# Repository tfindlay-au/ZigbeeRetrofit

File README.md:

# Zigbee Retrofit

### Purpose
This project provide a PCB that will retrofit into an M5Stack Zigbee Unit but replaces the CC2630 with the more common and better supported CC2531 chipset.

Designed in KiCad 6.0.9
The output board measures 50mm x 20mm and contains cutouts for mounting in the case /w lego fittings

The design incorporates a Tag-Connect 10 pad pogo pin (TC-2050-NL) footprint to write/flash firmware.
The design also incorporates a 4-pin Grove connector with UART interface for easy connection with M5Stack Atom products.

The design also uses the following symbols:
- 110990037: Seed Studio Grove connector
- CC2531F256RHAT: TI Chip Zigbee chip
- TC2050-IDC-NL: 10 pin flash connection
- U.FL-R-SMT-1_10: UFL antenna connector
- ECS-320-13-42-CKM-TR: 32 Mhz Crystal
- ECS-.327-12.5-34RR-TR: 32.768 kHz Crystal

### Next Steps
- Add USB port ?
- Add an RF shield to go over the chip

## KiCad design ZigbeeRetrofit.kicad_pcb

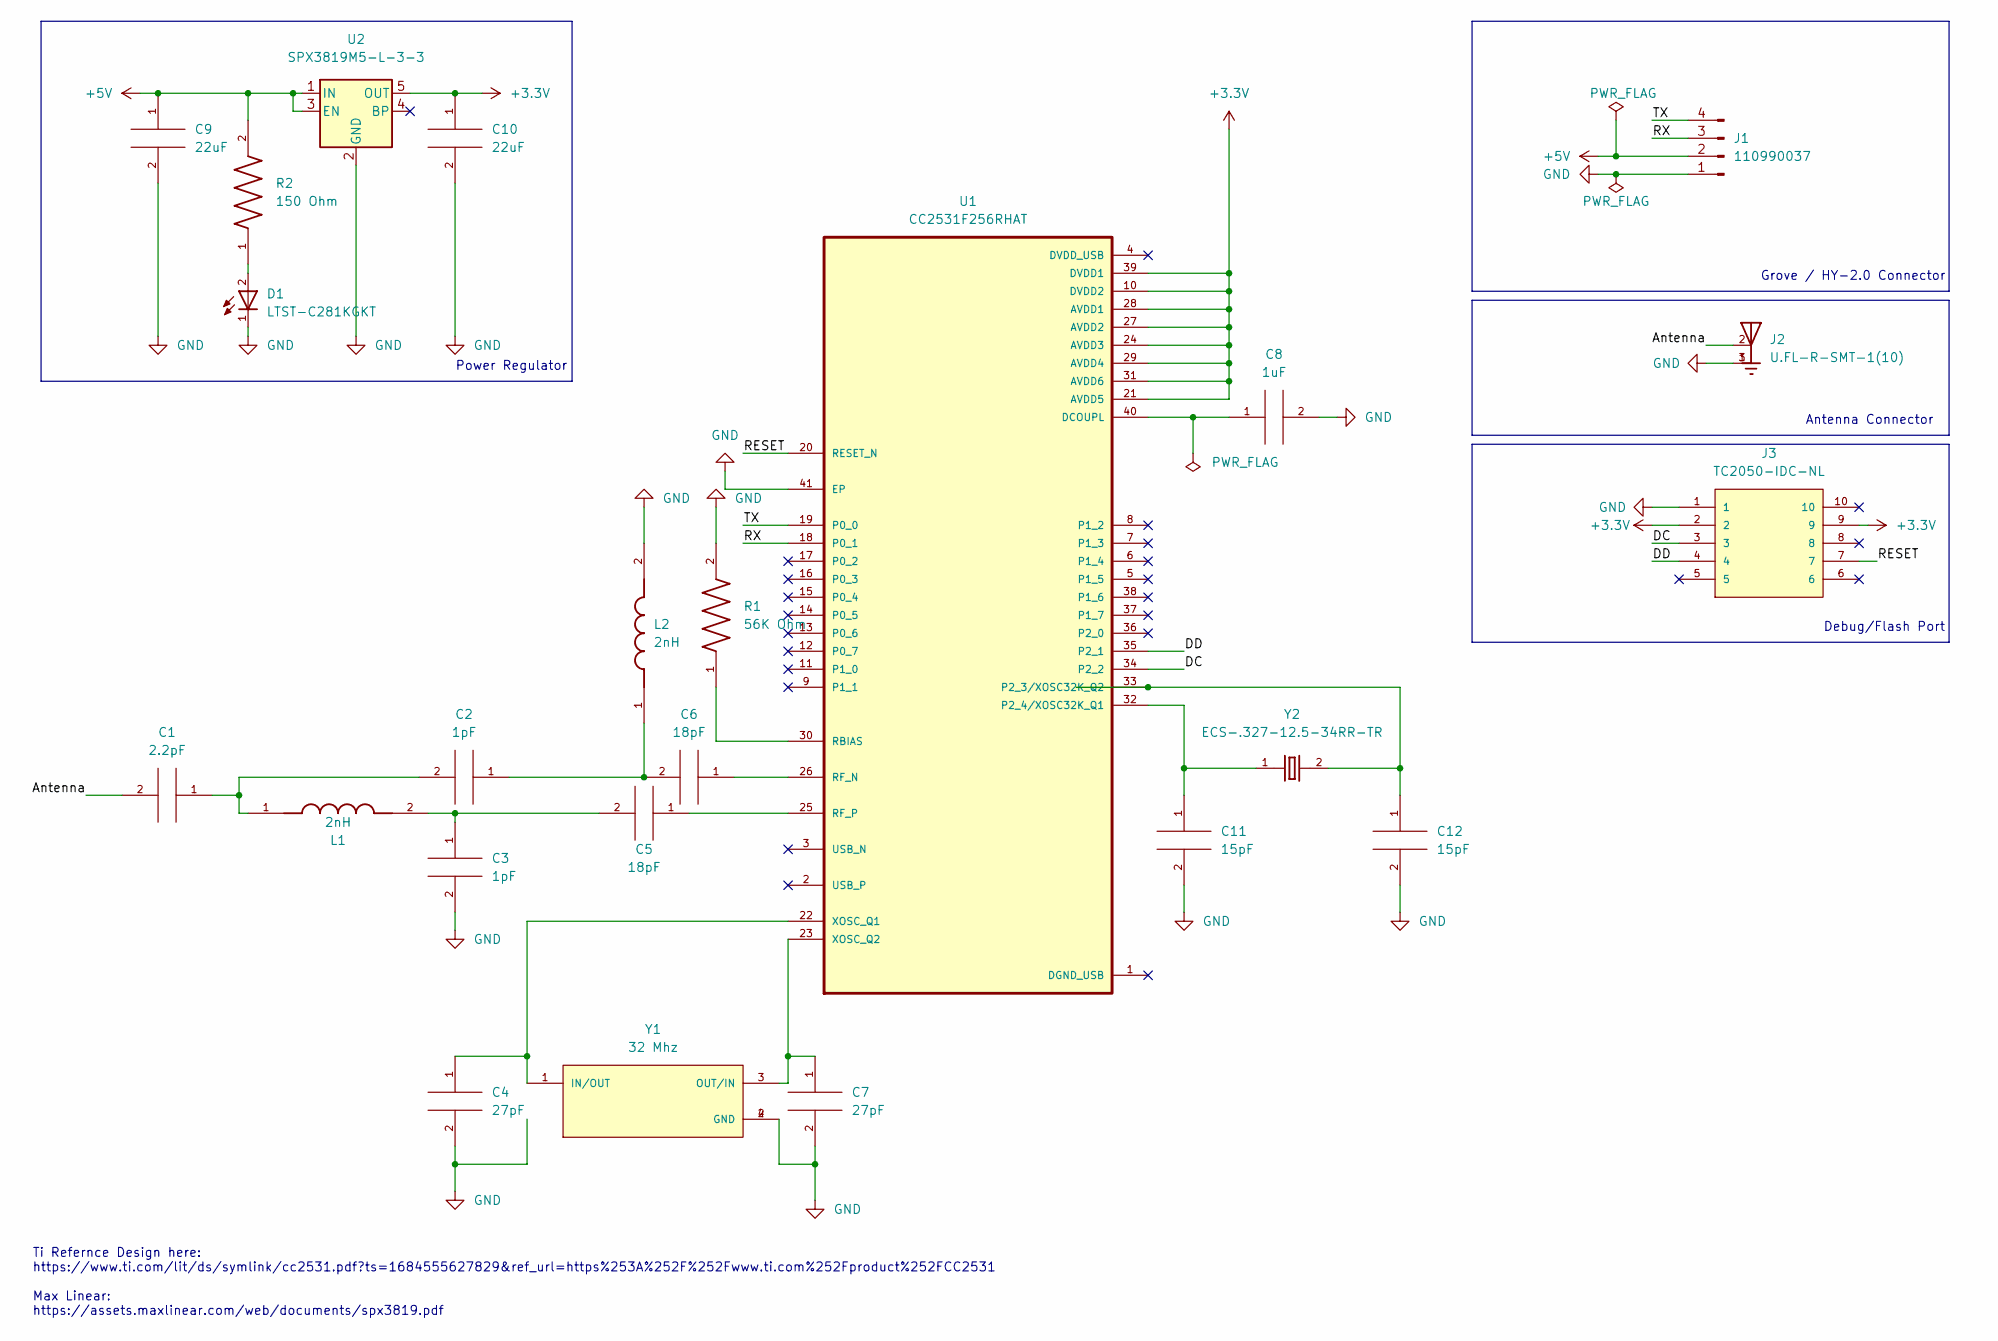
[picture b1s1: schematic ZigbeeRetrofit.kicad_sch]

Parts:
C1: 2.2pF; C_0402_1005Metric
C2, C3: 1pF; C_0402_1005Metric
C4, C7: 27pF; C_0402_1005Metric
C5, C6: 18pF; C_0402_1005Metric
C8: 1uF; C_0402_1005Metric
C9, C10: 22uF; C_0402_1005Metric
C11, C12: 15pF; C_0402_1005Metric
D1: LTST-C281KGKT; 0402(POL)
J1: 110990037; JST_PH_S4B-PH-K_1x04_P2.00mm_Horizontal; PARTREV A
J2: U.FL-R-SMT-1(10); HRS_U.FL-R-SMT-1(10)
J3: TC2050-IDC-NL; TAG-CONNECT_TC2050-IDC-NL; PARTREV A
L1, L2: 2nH; INDC1006X60N
R1: 56K Ohm; RES_ERJ-2GEJ563X; PARTREV 3/1/2020
R2: 150 Ohm; RES_ERJ-2GEJ151X; PARTREV 3/1/2020
U1: CC2531F256RHAT; QFN50P600X600X100-41N
U2: SPX3819M5-L-3-3; SOT-23-5
Y1: 32 Mhz; XTAL_ECS-320-13-42-CKM-TR; PARTREV 11/11
Y2: ECS-.327-12.5-34RR-TR; XTAL_ECS-.327-12.5-34RR-TR

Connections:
+3.3V: C10.1, J3.2, J3.9, U1.10 (DVDD2), U1.21 (AVDD5), U1.24 (AVDD3), U1.27 (AVDD2), U1.28 (AVDD1), U1.29 (AVDD4), U1.31 (AVDD6), U1.39 (DVDD1), U2.5 (OUT)
+5V: C9.1, J1.2, R2.2, U2.1 (IN), U2.3 (EN)
/Antenna: C1.2, J2.2
/DC: J3.3, U1.34 (P2_2)
/DD: J3.4, U1.35 (P2_1)
/RESET: J3.7, U1.20 (RESET_N)
/RX: J1.3, U1.18 (P0_1)
/TX: J1.4, U1.19 (P0_0)
GND: C3.2, C4.2, C7.2, C8.2, C9.2, C10.2, C11.2, C12.2, D1.1, J1.1, J2.1, J2.3, J3.1, L2.2, R1.2, U1.41 (EP), U2.2 (GND), Y1.2 (GND), Y1.4 (GND)
unnamed: C1.1, C2.2, L1.1
unnamed: C2.1, C6.2, L2.1
unnamed: C3.1, C5.2, L1.2
unnamed: C4.1, U1.22 (XOSC_Q1), Y1.1 (IN/OUT)
unnamed: C5.1, U1.25 (RF_P)
unnamed: C6.1, U1.26 (RF_N)
unnamed: C7.1, U1.23 (XOSC_Q2), Y1.3 (OUT/IN)
unnamed: C8.1, U1.40 (DCOUPL)
unnamed: C11.1, U1.32 (P2_4/XOSC32K_Q1), Y2.1
unnamed: C12.1, U1.33 (P2_3/XOSC32K_Q2), Y2.2
unnamed: D1.2, R2.1
unnamed: R1.1, U1.30 (RBIAS)

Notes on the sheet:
Antenna Connector
Grove / HY-2.0 Connector
Debug/Flash Port
Ti Refernce Design here: https://www.ti.com/lit/ds/symlink/cc2531.pdf?ts=1684555627829&ref_url=https%253A%252F%252Fwww.ti.com%252Fproduct%252FCC2531 Max Linear: https://assets.maxlinear.com/web/documents/spx3819.pdf
Power Regulator

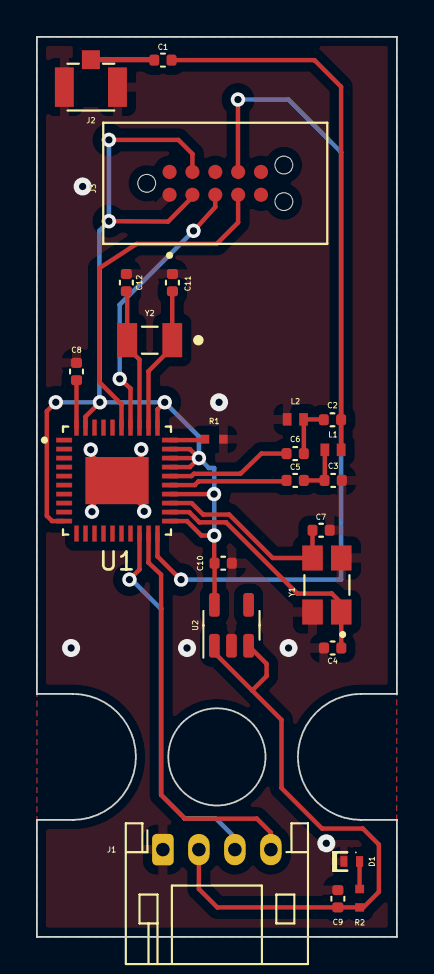
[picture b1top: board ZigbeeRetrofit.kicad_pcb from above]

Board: 2 copper layers, 20.0 x 50.0 mm, 24 parts (0 on the bottom side), 21 nets.

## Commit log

2023-08-14 Adding current schematic
2023-08-24 Updated crystals
2023-08-27 Updated Symbols to clear ERC
2023-08-28 Drafted first component layout for PCB
2023-08-28 Updated layout with 3d models
2023-09-03 Added ground
2023-09-04 Updated grove connector
2023-10-15 Revision 0.2 - Draft
2023-10-18 Revision 0.2 - Final
